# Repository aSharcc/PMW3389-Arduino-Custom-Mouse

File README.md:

# PMW3389 Custom DIY Mouse

A fully custom gaming mouse using a PixArt PMW3389.

2 versions. 3.3V/8MHz Arduino Pro Micro (ATmega32U4) and Seeed Studio XIAO ESP32C3.

I also intend for this mouse to be easily repairable.

Be sure to read [BOM.md](docs/BOM.md)

## Key Features

- High performance sensor: 16,000 DPI via PixArt PMW3389
- Modular and Repairable
	- Hotswap Main Switches: Uses Mill-Max 3305 so can be replaced with no soldering
	- Replaceable MCU: Mounted using through-hole pin headers
- Wireless and wired versions.
- Sensor communication through SPI

## Version Comparison

|Features|v2 (Wired)|v3 (Wireless)|
|---|---|---|
|MCU|3.3V/8MHz Arduino Pro Micro (ATmega32U4)|Seeed Studio XIAO ESP32C3|
|Connectivity|Micro-USB|Bluetooth / 2.4GHz Wireless|
|Power Source|Micro-USB|LiPo Battery|
|Production Files|[Files v2](https://github.com/aSharcc/PMW3389-Custom-Mouse/releases/tag/2.0)|[Files v3](https://github.com/aSharcc/PMW3389-Custom-Mouse/releases/tag/3.0)|

## How To Use

**DETAILED INSTRUCTIONS and BOM [HERE](docs/BOM.md)**

1. Order the PCB from a PCB manufacturer (e.g. JLCPCB) with files from specific release.
2. Either:
   - Order PCBA for the SMD components, or
   - Purchase the SMD components and hand solder them.
3. Purchase the components listed in the BOM that are not included in PCBA.
4. Hand solder/install the components not included in PCBA.
5. Download the PMW3389 library.
	- For Wired: [Arduino Library](Firmware/Arduino/README.md) for instructions.
	- For Wireless: **NOT COMPLETED**
6. Download Firmware
	- For Wired: [Arduino Firmware](https://github.com/aSharcc/PMW3389-Custom-Mouse/releases/download/2.0/Mouse.Firmware.ino)
	- For Wireless: **NOT COMPLETED**
7. Flash the firmware to the MCU.
8. Download and print the 3D models.
	- For Wired: [Top](https://github.com/aSharcc/PMW3389-Custom-Mouse/releases/download/2.0/Mouse.Shell.top.gcode.3mf) + [Bottom](https://github.com/aSharcc/PMW3389-Custom-Mouse/releases/download/2.0/Mouse.Shell.bottom.gcode.3mf) + [Scroll](https://github.com/aSharcc/PMW3389-Custom-Mouse/releases/download/2.0/Mouse.Shell.knob.gcode.3mf)
	- For Wireless: **NOT COMPLETED**
9. Add threaded heat inserts to the shell.
10. **For Wireless Only**:
	- **Not Completed** Will include power switch and battery stuff.
11. Assemble the mouse.

## Components

- Sensor: PixArt PMW3389 and LM19-LCT Lens

- MCU: 3.3V/8MHz Arduino Pro Micro (ATmega32U4) or Seeed Studio XIAO ESP32C3

- Switches: 2 x Huano Blue Shell Pink Dot Mouse Switches 

- Scroll Wheel: Rotary Encoder w/Switch (EC11)

- Hot Swap Socket for Switches: 6 x Mill-Max 3305

- SMD Components (0805)
	- 1 x 13 ohm resistor
	- 1 x 10k ohm resistor
	- 5 x 0.1uF capacitor
	- 3 x 10uF capacitor
	- 1 x 4.7uF capacitor
	- 1 x XC6206-1.8V LDO

- PTFE Mouse Skates

- Micro USB Cable for v2 or USB-C cable for v3 charging

- Mounting Hardware
	- 7 x Heat Inserts M2 x 3 x 3.2
	- 3 x M2 x 4 Screw
	- 4 x M2 x 7 Screw

- **FOR V3 ONLY**:
	- 500mAh battery with JST connector
	- SPDT / 1P2T PCB slide switch

## Pinout

|Component|Usage|v2 (3.3v/8MHz Pro Micro)|v3 (XIAO ESP32)|
|---|---|---|---|
|**PMW3389**|NCS|D10|D3|
||MOSI|D16 (MOSI)|D10 (MOSI)|
||MISO|D14 (MISO)|D9 (MISO)|
||SCLK|D15 (SCLK)|D8 (SCLK)|
||MOT|D2 (INT 1)|D4|
|**Rotary Encoder w/Switch**|Rotary Encoder A|D3 (INT 0)|D6|
||Rotary Encoder B|D7 (INT 6)|D0|
||Encoder Switch S2 (Middle Click)|D8|D7|
|**Switches**|Switch 1 (Left Click)|D4|D1|
||Switch 2 (Right Click)|D9|D2|

## Documentation & Credits

- [Build & Design Log](CHANGELOG.md)
- [Third-Party Credits & Libraries](CREDITS.md)
- [MIT License](LICENSE)

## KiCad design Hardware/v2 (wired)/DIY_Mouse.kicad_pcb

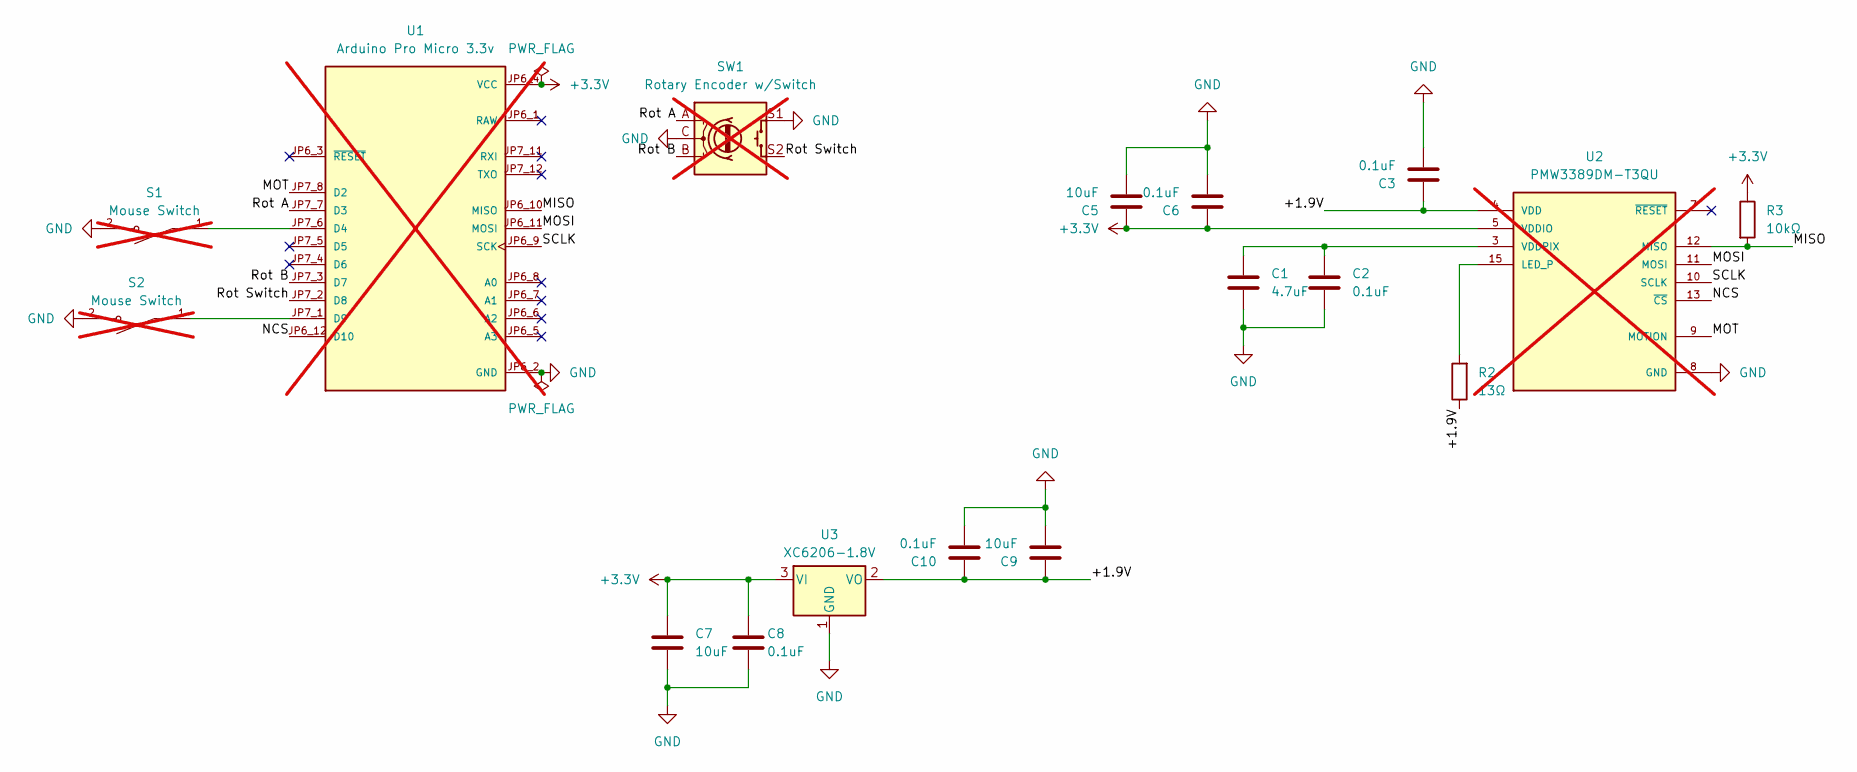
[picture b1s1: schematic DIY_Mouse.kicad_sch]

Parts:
C1: 4.7uF; C_0805_2012Metric_Pad1.18x1.45mm_HandSolder; LCSC Part # C354262
C2, C3, C6, C8, C10: 0.1uF; C_0805_2012Metric_Pad1.18x1.45mm_HandSolder; LCSC Part # C519981
C5, C7, C9: 10uF; C_0805_2012Metric_Pad1.18x1.45mm_HandSolder; LCSC Part # C326595
R2: 13Ω; R_0805_2012Metric_Pad1.20x1.40mm_HandSolder; LCSC Part # C2933313
R3: 10kΩ; R_0805_2012Metric_Pad1.20x1.40mm_HandSolder; LCSC Part # C881248
S1, S2: Mouse Switch; SW_D2FC-F-7N_100M_; PARTREV 2023-2024; not fitted
SW1: Rotary Encoder w/Switch; RotaryEncoder_Alps_EC11E-Switch_Vertical_H20mm; not fitted
U1: Arduino Pro Micro 3.3v; MODULE_DEV-12587; PARTREV 2/12/2015; not fitted
U2: PMW3389DM-T3QU; PMW3360; MANUFACTURER_PART_NUMBER PMW3360DM-T2QU; not fitted
U3: XC6206-1.8V; SOT-23; LCSC Part # C49195704

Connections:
+3.3V: C5.1, C6.2, C7.2, C8.1, R3.1, U1.JP6_4 (VCC), U2.5 (VDDIO), U3.3 (VI)
/+1.9V: C3.2, C9.2, C10.1, R2.1, U2.4 (VDD), U3.2 (VO)
/MISO: R3.2, U1.JP6_10 (MISO), U2.12 (MISO)
/MOSI: U1.JP6_11 (MOSI), U2.11 (MOSI)
/MOT: U1.JP7_8 (D2), U2.9 (MOTION)
/NCS: U1.JP6_12 (D10), U2.13 (~CS)
/Rot A: SW1.A, U1.JP7_7 (D3)
/Rot B: SW1.B, U1.JP7_3 (D7)
/Rot Switch: SW1.S2, U1.JP7_2 (D8)
/SCLK: U1.JP6_9 (SCK), U2.10 (SCLK)
GND: C1.1, C2.2, C3.1, C5.2, C6.1, C7.1, C8.2, C9.1, C10.2, S1.2, S2.2, SW1.C, SW1.S1, U1.JP6_2 (GND), U1.JP7_9 (GND), U1.JP7_10 (GND), U2.8 (GND), U3.1 (GND)
unnamed: S1.1, U1.JP7_6 (D4)
unnamed: S2.1, U1.JP7_1 (D9)
unnamed: R2.2, U2.15 (LED_P)
unnamed: C1.2, C2.1, U2.3 (VDDPIX)

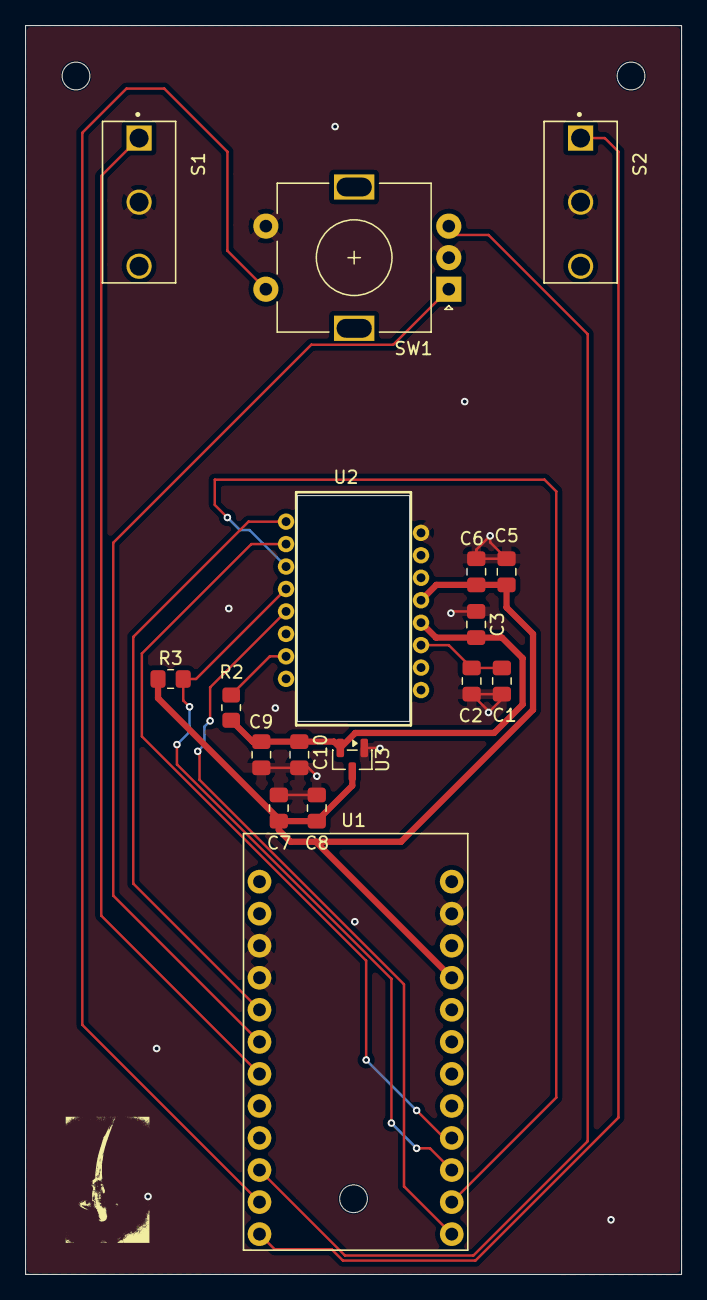
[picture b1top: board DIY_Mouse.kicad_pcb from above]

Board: 2 copper layers, 52.0 x 99.0 mm, 17 parts (0 on the bottom side), 15 nets.

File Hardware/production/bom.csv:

Designator,Footprint,Quantity,Value,LCSC Part #
C1,0805,1,4.7uF,
"C10, C2, C3, C6, C8",0805,5,0.1uF,
"C5, C7, C9",0805,3,10uF,
R2,0805,1,13Ω,
R3,0805,1,10kΩ,
"S1, S2",SW_D2FC-F-7N_100M_,2,Mouse Switch,
SW1,RotaryEncoder_Alps_EC11E-Switch_Vertical_H20mm,1,Rotary Encoder w/Switch,
U1,MODULE_DEV-12587,1,Arduino Pro Micro 3.3v,
U2,PMW3360,1,PMW3389DM-T3QU,
U3,SOT-23,1,XC6206P332MR-G,

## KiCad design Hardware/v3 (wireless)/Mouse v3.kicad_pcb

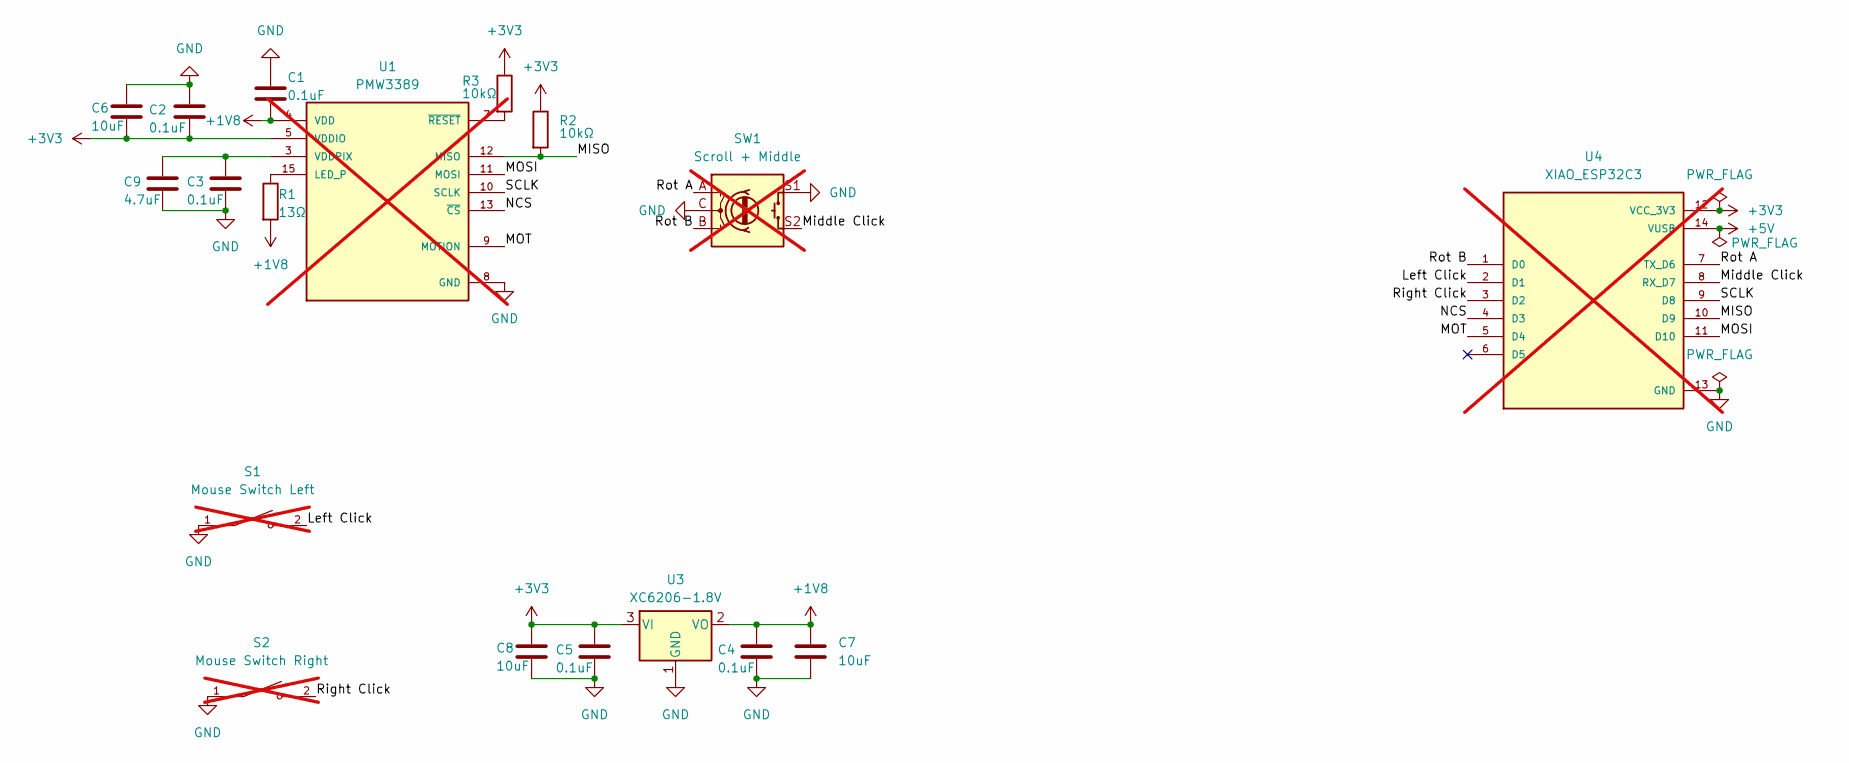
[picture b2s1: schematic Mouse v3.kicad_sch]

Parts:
C1, C2, C3, C4, C5: 0.1uF; C_0805_2012Metric_Pad1.18x1.45mm_HandSolder
C6, C7, C8: 10uF; C_0805_2012Metric_Pad1.18x1.45mm_HandSolder
C9: 4.7uF; C_0805_2012Metric_Pad1.18x1.45mm_HandSolder
R1: 13Ω; R_0805_2012Metric_Pad1.20x1.40mm_HandSolder
R2, R3: 10kΩ; R_0805_2012Metric_Pad1.20x1.40mm_HandSolder
S1: Mouse Switch Left; SW_D2FC-F-7N_100M_; PARTREV 2023-2024; not fitted
S2: Mouse Switch Right; SW_D2FC-F-7N_100M_; PARTREV 2023-2024; not fitted
SW1: Scroll + Middle; RotaryEncoder_Alps_EC11E-Switch_Vertical_H20mm; not fitted
U1: PMW3389; PMW3360; MANUFACTURER_PART_NUMBER PMW3360DM-T2QU; not fitted
U3: XC6206-1.8V; SOT-23-3
U4: XIAO_ESP32C3; MODULE_XIAO_ESP32C3; PARTREV 23/05/2022; not fitted

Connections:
+1V8: C1.2, C4.1, C7.1, R1.2, U1.4 (VDD), U3.2 (VO)
+3V3: C2.2, C5.1, C6.2, C8.1, R2.1, R3.1, U1.5 (VDDIO), U3.3 (VI), U4.12 (VCC_3V3)
+5V: U4.14 (VUSB)
/Left Click: S1.2, U4.2 (D1)
/MISO: R2.2, U1.12 (MISO), U4.10 (D9)
/MOSI: U1.11 (MOSI), U4.11 (D10)
/MOT: U1.9 (MOTION), U4.5 (D4)
/Middle Click: SW1.S2, U4.8 (RX_D7)
/NCS: U1.13 (~CS), U4.4 (D3)
/Right Click: S2.2, U4.3 (D2)
/Rot A: SW1.A, U4.7 (TX_D6)
/Rot B: SW1.B, U4.1 (D0)
/SCLK: U1.10 (SCLK), U4.9 (D8)
GND: C1.1, C2.1, C3.2, C4.2, C5.2, C6.1, C7.2, C8.2, C9.2, S1.1, S2.1, SW1.C, SW1.S1, U1.8 (GND), U3.1 (GND), U4.13 (GND)
unnamed: R1.1, U1.15 (LED_P)
unnamed: C3.1, C9.1, U1.3 (VDDPIX)
unnamed: R3.2, U1.7 (~RESET)

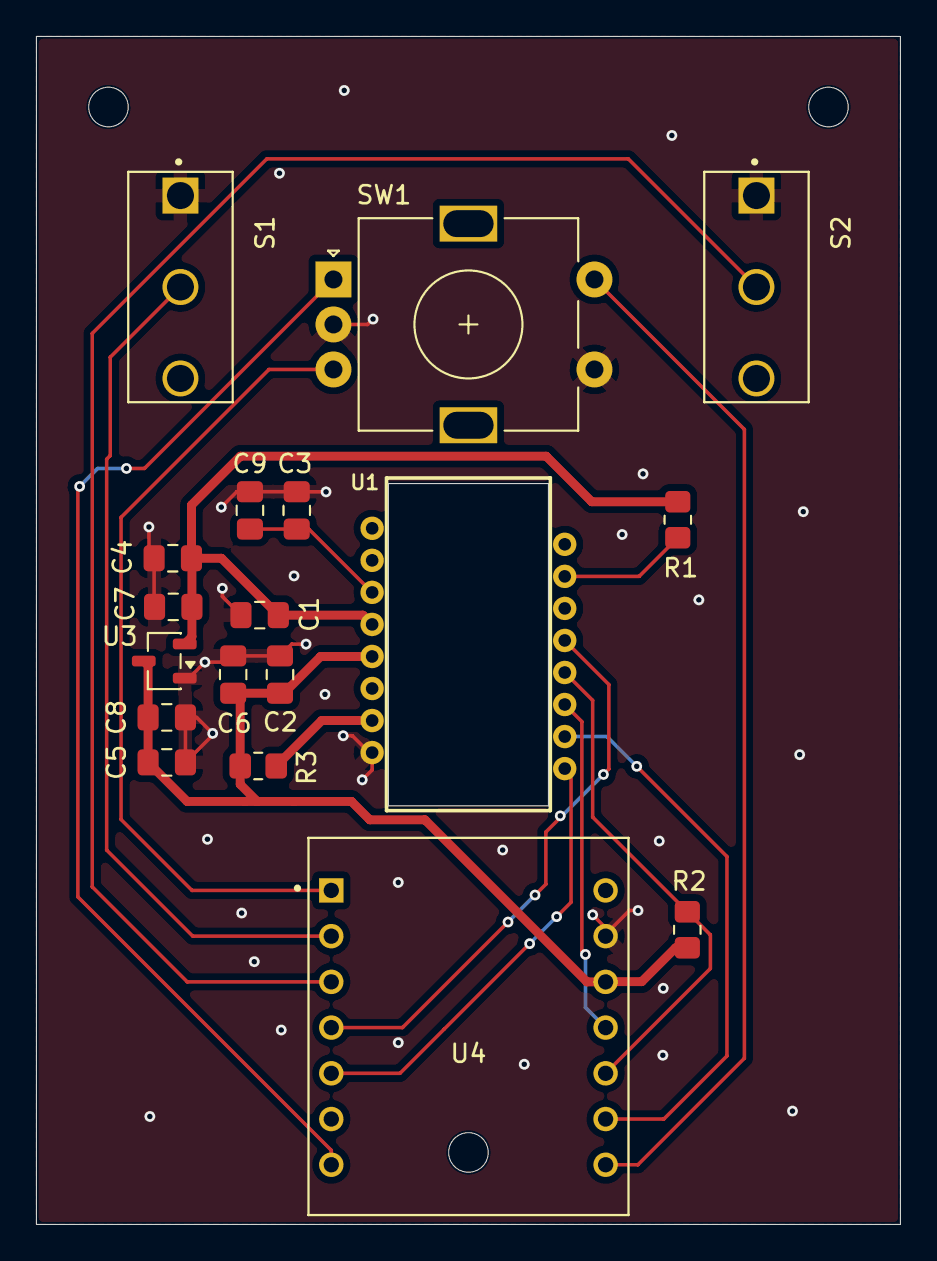
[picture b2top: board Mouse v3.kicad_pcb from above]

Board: 2 copper layers, 48.0 x 66.0 mm, 18 parts (0 on the bottom side), 16 nets.
